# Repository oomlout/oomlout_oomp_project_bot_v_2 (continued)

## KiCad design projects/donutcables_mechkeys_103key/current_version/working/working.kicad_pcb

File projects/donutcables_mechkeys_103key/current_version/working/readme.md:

# mechkeys
 
## summary 
* id: donutcables_mechkeys_103key
* user: donutcables
* name: mechkeys
* board: 103key
* repo: https://github.com/DonutCables/mechkeys
* src_file_repo_kicad_pcb: 103key-project/103key.kicad_pcb
* src_file_repo_kicad_pcb_link: https://github.com/DonutCables/mechkeys/tree/master/103key-project/103key.kicad_pcb

* src_file_repo_sch: 103key-project/103key.sch
* src_file_repo_sch_link: https://github.com/DonutCables/mechkeys/tree/master/103key-project/103key.sch
* full details link: https://github.com/oomlout/oomlout_oomp_project_bot_v_2/tree/main/projects/donutcables_mechkeys_103key/current_version/working

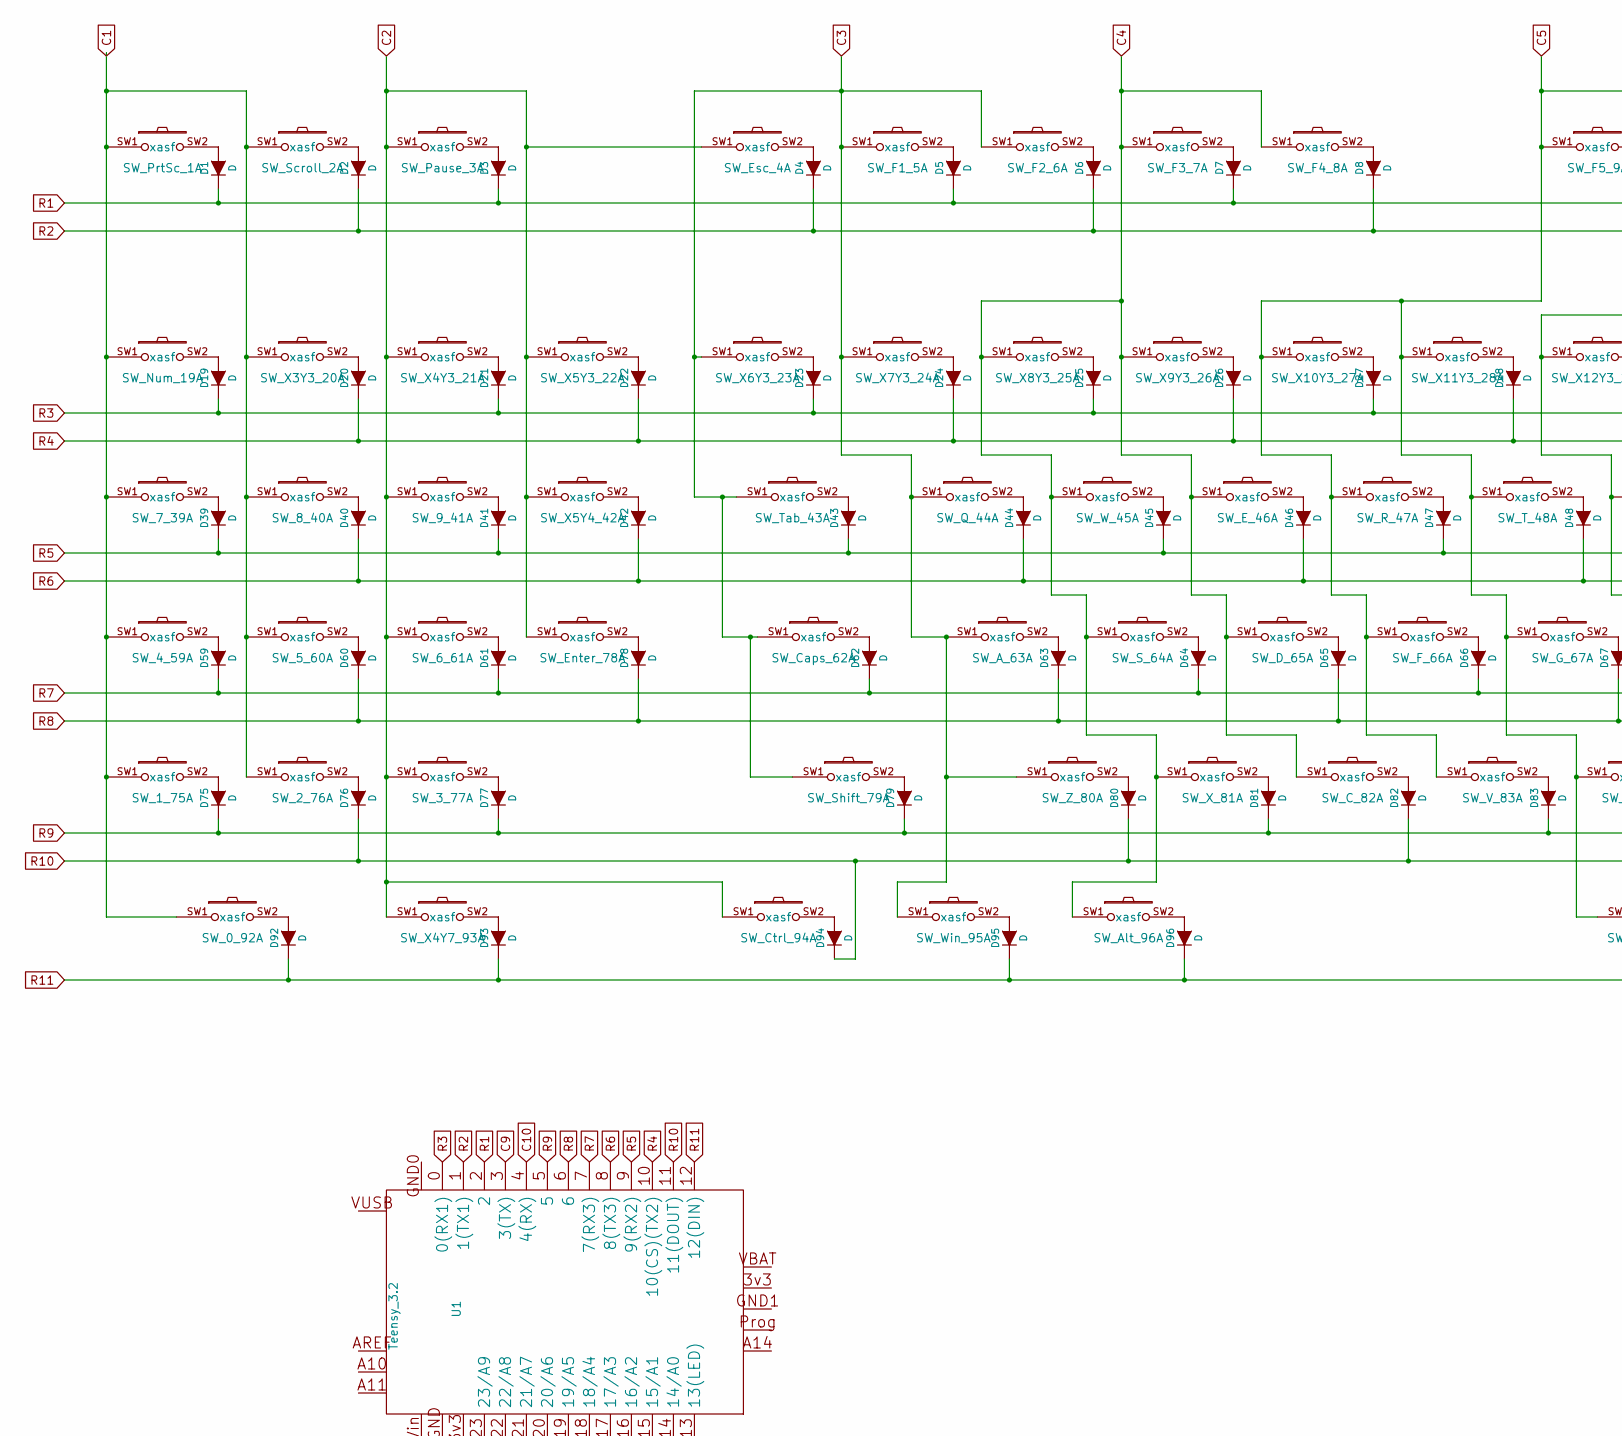
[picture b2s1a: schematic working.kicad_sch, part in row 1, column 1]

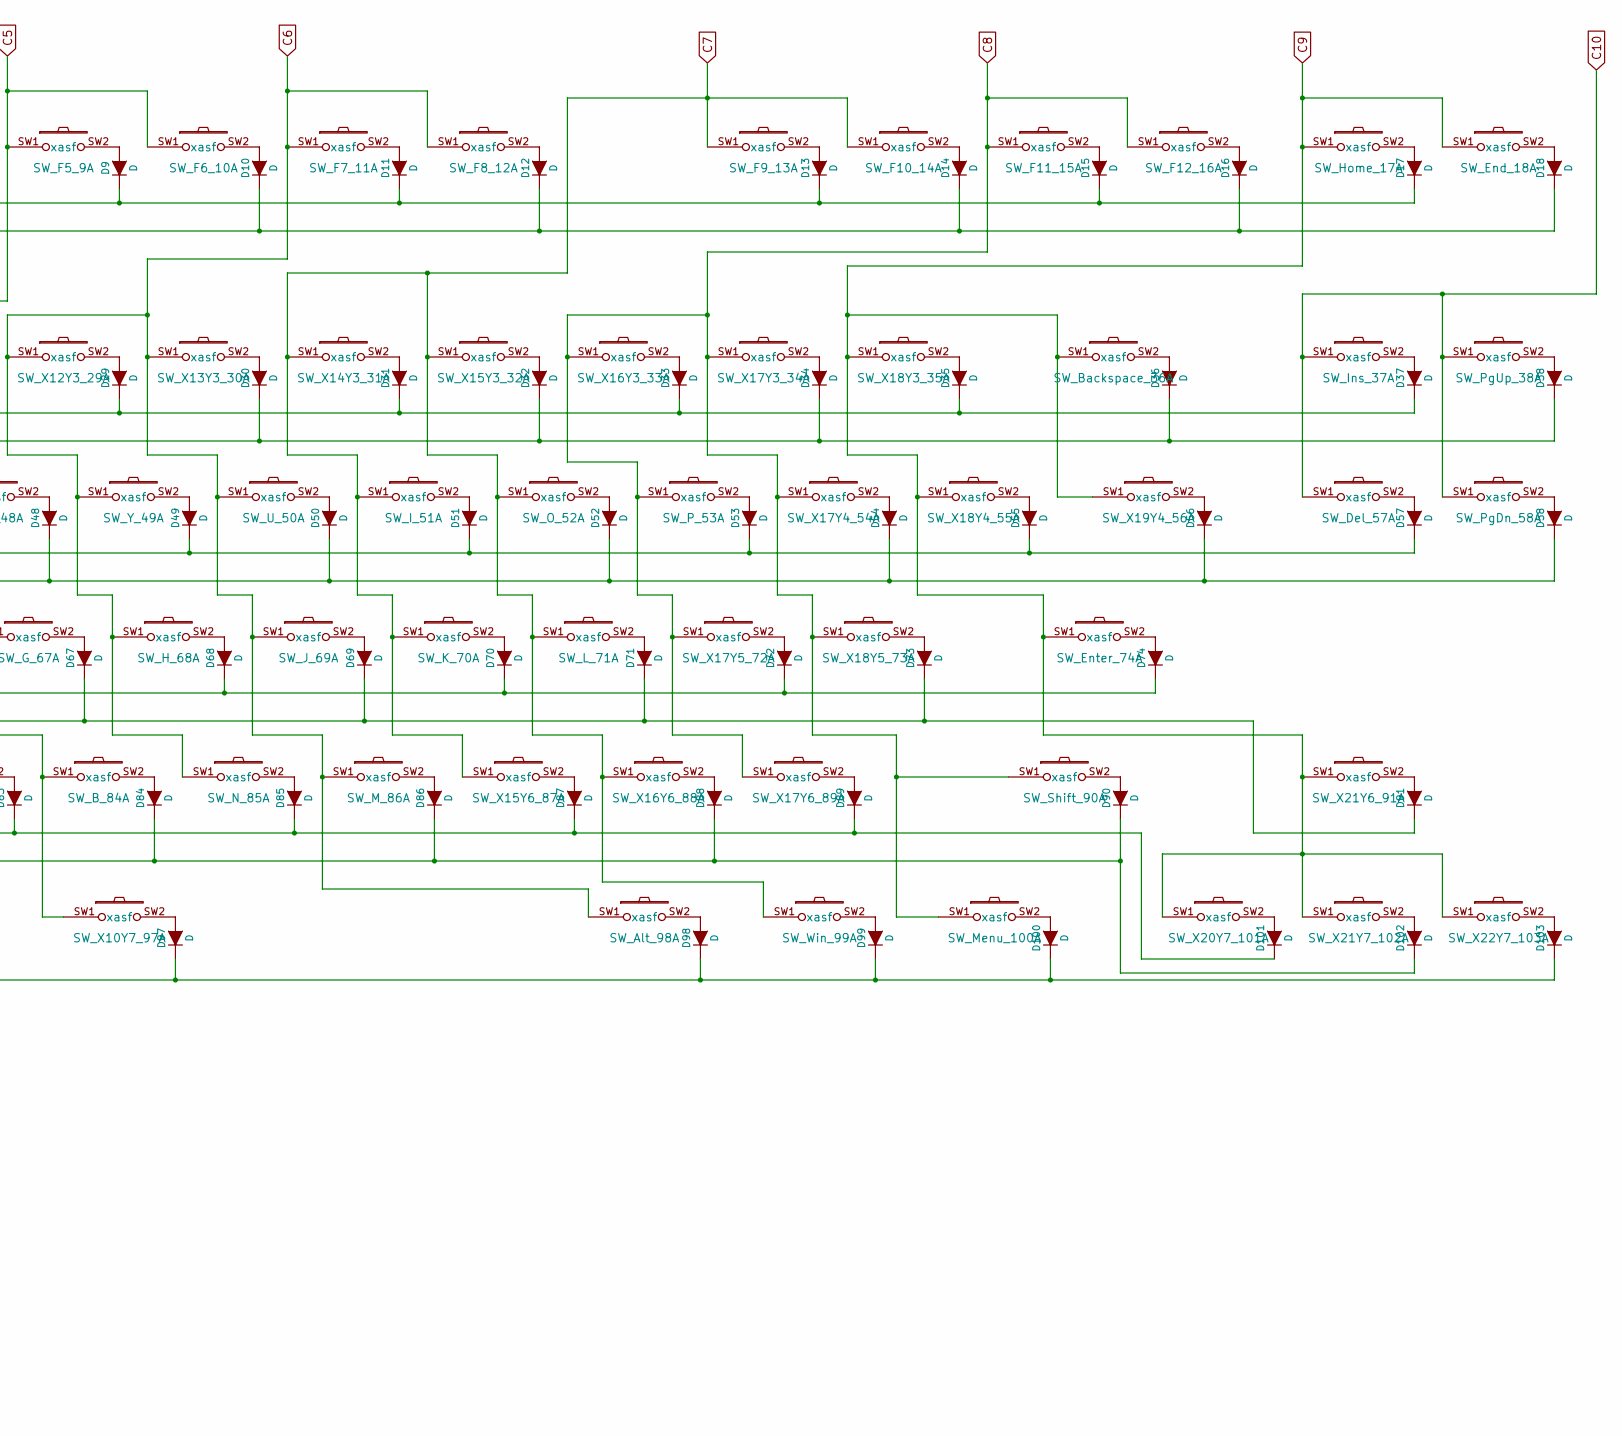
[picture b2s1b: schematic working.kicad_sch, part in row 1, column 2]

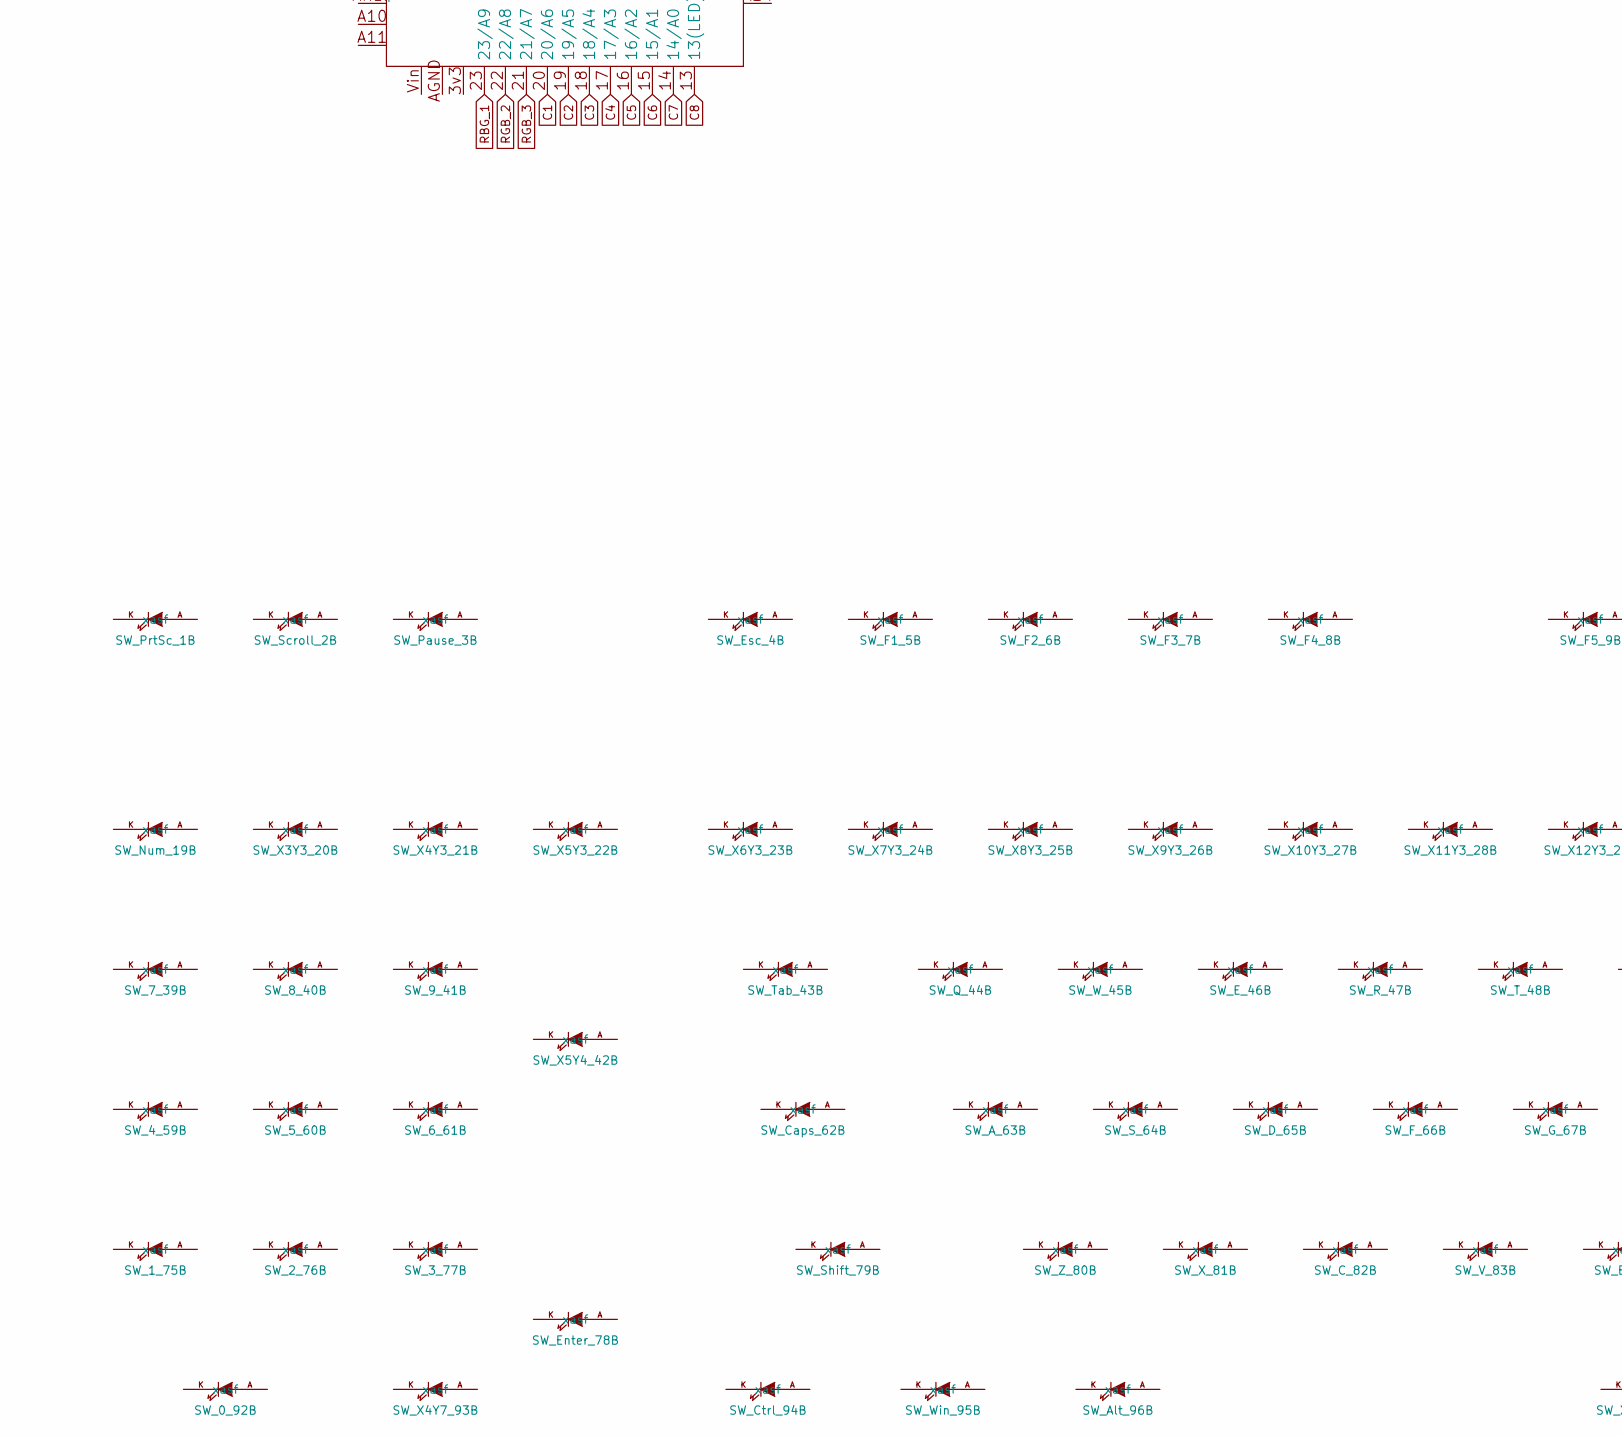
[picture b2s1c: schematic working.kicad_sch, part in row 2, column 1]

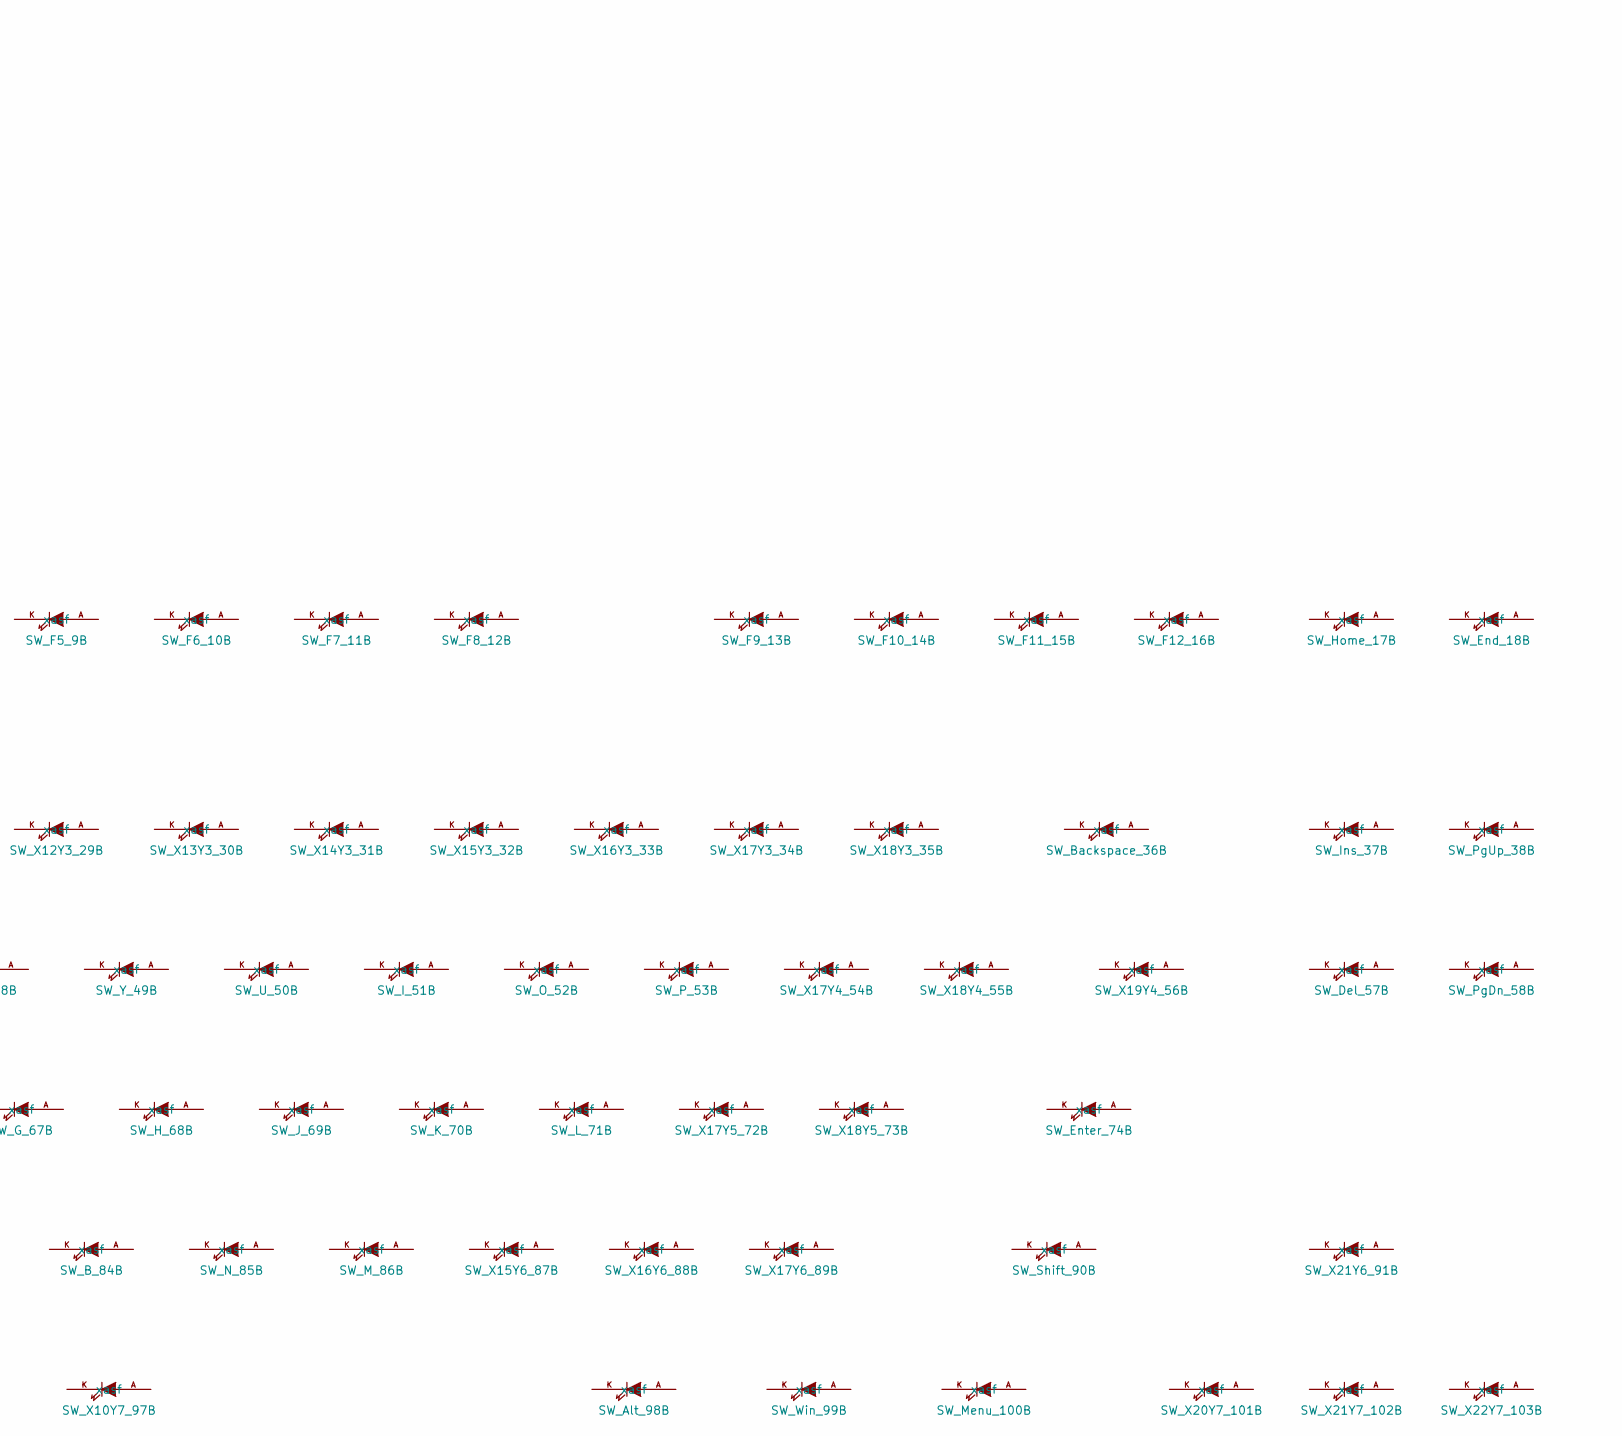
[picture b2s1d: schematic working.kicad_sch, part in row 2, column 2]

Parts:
D1, D2, D3, D4, D5, D6, D7, D8, D9, D10, D11, D12, D13, D14, D15, D16, D17, D18, D19, D20, D21, D22, D23, D24, D25, D26, D27, D28, D29, D30, D31, D32, D33, D34, D35, D36, D37, D38, D39, D40, D41, D42, D43, D44, D45, D46, D47, D48, D49, D50, D51, D52, D53, D54, D55, D56, D57, D58, D59, D60, D61, D62, D63, D64, D65, D66, D67, D68, D69, D70, D71, D72, D73, D74, D75, D76, D77, D78, D79, D80, D81, D82, D83, D84, D85, D86, D87, D88, D89, D90, D91, D92, D93, D94, D95, D96, D97, D98, D99, D100, D101, D102, D103: D
SW_0_92, SW_1_75, SW_2_76, SW_3_77, SW_4_59, SW_5_60, SW_6_61, SW_7_39, SW_8_40, SW_9_41: MX_LED
SW_A_63: MX_LED
SW_Alt_96, SW_Alt_98: MX_LED
SW_B_84: MX_LED
SW_Backspace_36: MX_LED
SW_C_82: MX_LED
SW_Caps_62: MX_LED
SW_Ctrl_94: MX_LED
SW_D_65: MX_LED
SW_Del_57: MX_LED
SW_E_46: MX_LED
SW_End_18: MX_LED
SW_Enter_74, SW_Enter_78: MX_LED
SW_Esc_4: MX_LED
SW_F1_5, SW_F2_6, SW_F3_7, SW_F4_8, SW_F5_9, SW_F6_10, SW_F7_11, SW_F8_12, SW_F9_13, SW_F10_14, SW_F11_15, SW_F12_16: MX_LED
SW_F_66: MX_LED
SW_G_67: MX_LED
SW_H_68: MX_LED
SW_Home_17: MX_LED
SW_I_51: MX_LED
SW_Ins_37: MX_LED
SW_J_69: MX_LED
SW_K_70: MX_LED
SW_L_71: MX_LED
SW_M_86: MX_LED
SW_Menu_100: MX_LED
SW_N_85: MX_LED
SW_Num_19: MX_LED
SW_O_52: MX_LED
SW_P_53: MX_LED
SW_Pause_3: MX_LED
SW_PgDn_58: MX_LED
SW_PgUp_38: MX_LED
SW_PrtSc_1: MX_LED
SW_Q_44: MX_LED
SW_R_47: MX_LED
SW_S_64: MX_LED
SW_Scroll_2: MX_LED
SW_Shift_79, SW_Shift_90: MX_LED
SW_T_48: MX_LED
SW_Tab_43: MX_LED
SW_U_50: MX_LED
SW_V_83: MX_LED
SW_W_45: MX_LED
SW_Win_95, SW_Win_99: MX_LED
SW_X3Y3_20, SW_X4Y3_21, SW_X4Y7_93, SW_X5Y3_22, SW_X5Y4_42, SW_X6Y3_23, SW_X7Y3_24, SW_X8Y3_25, SW_X9Y3_26, SW_X10Y3_27, SW_X10Y7_97, SW_X11Y3_28, SW_X12Y3_29, SW_X13Y3_30, SW_X14Y3_31, SW_X15Y3_32, SW_X15Y6_87, SW_X16Y3_33, SW_X16Y6_88, SW_X17Y3_34, SW_X17Y4_54, SW_X17Y5_72, SW_X17Y6_89, SW_X18Y3_35, SW_X18Y4_55, SW_X18Y5_73, SW_X19Y4_56, SW_X20Y7_101, SW_X21Y6_91, SW_X21Y7_102, SW_X22Y7_103: MX_LED
SW_X_81: MX_LED
SW_Y_49: MX_LED
SW_Z_80: MX_LED
U1: Teensy_3.2; Teensy3.2

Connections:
C1: SW_0_92.SW1, SW_1_75.SW1, SW_2_76.SW1, SW_4_59.SW1, SW_5_60.SW1, SW_7_39.SW1, SW_8_40.SW1, SW_Num_19.SW1, SW_PrtSc_1.SW1, SW_Scroll_2.SW1, SW_X3Y3_20.SW1, U1.20 (20/A6)
C2: SW_3_77.SW1, SW_6_61.SW1, SW_9_41.SW1, SW_Ctrl_94.SW1, SW_Enter_78.SW1, SW_Esc_4.SW1, SW_Pause_3.SW1, SW_X4Y3_21.SW1, SW_X4Y7_93.SW1, SW_X5Y3_22.SW1, SW_X5Y4_42.SW1, U1.19 (19/A5)
C3: SW_A_63.SW1, SW_Caps_62.SW1, SW_F1_5.SW1, SW_F2_6.SW1, SW_Q_44.SW1, SW_Shift_79.SW1, SW_Tab_43.SW1, SW_Win_95.SW1, SW_X6Y3_23.SW1, SW_X7Y3_24.SW1, SW_Z_80.SW1, U1.18 (18/A4)
C4: SW_Alt_96.SW1, SW_C_82.SW1, SW_D_65.SW1, SW_E_46.SW1, SW_F3_7.SW1, SW_F4_8.SW1, SW_S_64.SW1, SW_W_45.SW1, SW_X8Y3_25.SW1, SW_X9Y3_26.SW1, SW_X_81.SW1, U1.17 (17/A3)
C5: SW_B_84.SW1, SW_F5_9.SW1, SW_F6_10.SW1, SW_F_66.SW1, SW_G_67.SW1, SW_R_47.SW1, SW_T_48.SW1, SW_V_83.SW1, SW_X10Y3_27.SW1, SW_X10Y7_97.SW1, SW_X11Y3_28.SW1, U1.16 (16/A2)
C6: SW_Alt_98.SW1, SW_F7_11.SW1, SW_F8_12.SW1, SW_H_68.SW1, SW_J_69.SW1, SW_M_86.SW1, SW_N_85.SW1, SW_U_50.SW1, SW_X12Y3_29.SW1, SW_X13Y3_30.SW1, SW_Y_49.SW1, U1.15 (15/A1)
C7: SW_F9_13.SW1, SW_F10_14.SW1, SW_I_51.SW1, SW_K_70.SW1, SW_L_71.SW1, SW_O_52.SW1, SW_Win_99.SW1, SW_X14Y3_31.SW1, SW_X15Y3_32.SW1, SW_X15Y6_87.SW1, SW_X16Y6_88.SW1, U1.14 (14/A0)
C8: SW_F11_15.SW1, SW_F12_16.SW1, SW_Menu_100.SW1, SW_P_53.SW1, SW_Shift_90.SW1, SW_X16Y3_33.SW1, SW_X17Y3_34.SW1, SW_X17Y4_54.SW1, SW_X17Y5_72.SW1, SW_X17Y6_89.SW1, SW_X18Y5_73.SW1, U1.13 (13(LED))
C9: SW_Backspace_36.SW1, SW_End_18.SW1, SW_Enter_74.SW1, SW_Home_17.SW1, SW_X18Y3_35.SW1, SW_X18Y4_55.SW1, SW_X19Y4_56.SW1, SW_X20Y7_101.SW1, SW_X21Y6_91.SW1, SW_X21Y7_102.SW1, SW_X22Y7_103.SW1, U1.3 (3(TX))
C10: SW_Del_57.SW1, SW_Ins_37.SW1, SW_PgDn_58.SW1, SW_PgUp_38.SW1, U1.4 (4(RX))
unnamed: D1.2 (A), SW_PrtSc_1.SW2
unnamed: D2.2 (A), SW_Scroll_2.SW2
unnamed: D3.2 (A), SW_Pause_3.SW2
unnamed: D4.2 (A), SW_Esc_4.SW2
unnamed: D5.2 (A), SW_F1_5.SW2
unnamed: D6.2 (A), SW_F2_6.SW2
unnamed: D7.2 (A), SW_F3_7.SW2
unnamed: D8.2 (A), SW_F4_8.SW2
unnamed: D9.2 (A), SW_F5_9.SW2
unnamed: D10.2 (A), SW_F6_10.SW2
unnamed: D11.2 (A), SW_F7_11.SW2
unnamed: D12.2 (A), SW_F8_12.SW2
unnamed: D13.2 (A), SW_F9_13.SW2
unnamed: D14.2 (A), SW_F10_14.SW2
unnamed: D15.2 (A), SW_F11_15.SW2
unnamed: D16.2 (A), SW_F12_16.SW2
unnamed: D17.2 (A), SW_Home_17.SW2
unnamed: D18.2 (A), SW_End_18.SW2
unnamed: D19.2 (A), SW_Num_19.SW2
unnamed: D20.2 (A), SW_X3Y3_20.SW2
unnamed: D21.2 (A), SW_X4Y3_21.SW2
unnamed: D22.2 (A), SW_X5Y3_22.SW2
unnamed: D23.2 (A), SW_X6Y3_23.SW2
unnamed: D24.2 (A), SW_X7Y3_24.SW2
unnamed: D25.2 (A), SW_X8Y3_25.SW2
unnamed: D26.2 (A), SW_X9Y3_26.SW2
unnamed: D27.2 (A), SW_X10Y3_27.SW2
unnamed: D28.2 (A), SW_X11Y3_28.SW2
unnamed: D29.2 (A), SW_X12Y3_29.SW2
unnamed: D30.2 (A), SW_X13Y3_30.SW2
unnamed: D31.2 (A), SW_X14Y3_31.SW2
unnamed: D32.2 (A), SW_X15Y3_32.SW2
unnamed: D33.2 (A), SW_X16Y3_33.SW2
unnamed: D34.2 (A), SW_X17Y3_34.SW2
unnamed: D35.2 (A), SW_X18Y3_35.SW2
unnamed: D36.2 (A), SW_Backspace_36.SW2
unnamed: D37.2 (A), SW_Ins_37.SW2
unnamed: D38.2 (A), SW_PgUp_38.SW2
unnamed: D39.2 (A), SW_7_39.SW2
unnamed: D40.2 (A), SW_8_40.SW2
unnamed: D41.2 (A), SW_9_41.SW2
unnamed: D42.2 (A), SW_X5Y4_42.SW2
unnamed: D43.2 (A), SW_Tab_43.SW2
unnamed: D44.2 (A), SW_Q_44.SW2
unnamed: D45.2 (A), SW_W_45.SW2
unnamed: D46.2 (A), SW_E_46.SW2
unnamed: D47.2 (A), SW_R_47.SW2
unnamed: D48.2 (A), SW_T_48.SW2
unnamed: D49.2 (A), SW_Y_49.SW2
unnamed: D50.2 (A), SW_U_50.SW2
unnamed: D51.2 (A), SW_I_51.SW2
unnamed: D52.2 (A), SW_O_52.SW2
unnamed: D53.2 (A), SW_P_53.SW2
unnamed: D54.2 (A), SW_X17Y4_54.SW2
unnamed: D55.2 (A), SW_X18Y4_55.SW2
unnamed: D56.2 (A), SW_X19Y4_56.SW2
unnamed: D57.2 (A), SW_Del_57.SW2
unnamed: D58.2 (A), SW_PgDn_58.SW2
unnamed: D59.2 (A), SW_4_59.SW2
unnamed: D60.2 (A), SW_5_60.SW2
unnamed: D61.2 (A), SW_6_61.SW2
unnamed: D62.2 (A), SW_Caps_62.SW2
unnamed: D63.2 (A), SW_A_63.SW2
unnamed: D64.2 (A), SW_S_64.SW2
unnamed: D65.2 (A), SW_D_65.SW2
unnamed: D66.2 (A), SW_F_66.SW2
unnamed: D67.2 (A), SW_G_67.SW2
unnamed: D68.2 (A), SW_H_68.SW2
unnamed: D69.2 (A), SW_J_69.SW2
unnamed: D70.2 (A), SW_K_70.SW2
unnamed: D71.2 (A), SW_L_71.SW2
unnamed: D72.2 (A), SW_X17Y5_72.SW2
unnamed: D73.2 (A), SW_X18Y5_73.SW2
unnamed: D74.2 (A), SW_Enter_74.SW2
unnamed: D75.2 (A), SW_1_75.SW2
unnamed: D76.2 (A), SW_2_76.SW2
unnamed: D77.2 (A), SW_3_77.SW2
unnamed: D78.2 (A), SW_Enter_78.SW2
unnamed: D79.2 (A), SW_Shift_79.SW2
unnamed: D80.2 (A), SW_Z_80.SW2
unnamed: D81.2 (A), SW_X_81.SW2
unnamed: D82.2 (A), SW_C_82.SW2
unnamed: D83.2 (A), SW_V_83.SW2
unnamed: D84.2 (A), SW_B_84.SW2
unnamed: D85.2 (A), SW_N_85.SW2
unnamed: D86.2 (A), SW_M_86.SW2
unnamed: D87.2 (A), SW_X15Y6_87.SW2
unnamed: D88.2 (A), SW_X16Y6_88.SW2
unnamed: D89.2 (A), SW_X17Y6_89.SW2
unnamed: D90.2 (A), SW_Shift_90.SW2
unnamed: D91.2 (A), SW_X21Y6_91.SW2
unnamed: D92.2 (A), SW_0_92.SW2
unnamed: D93.2 (A), SW_X4Y7_93.SW2
unnamed: D94.2 (A), SW_Ctrl_94.SW2
unnamed: D95.2 (A), SW_Win_95.SW2
unnamed: D96.2 (A), SW_Alt_96.SW2
unnamed: D97.2 (A), SW_X10Y7_97.SW2
unnamed: D98.2 (A), SW_Alt_98.SW2
unnamed: D99.2 (A), SW_Win_99.SW2
unnamed: D100.2 (A), SW_Menu_100.SW2
unnamed: D101.2 (A), SW_X20Y7_101.SW2
unnamed: D102.2 (A), SW_X21Y7_102.SW2
unnamed: D103.2 (A), SW_X22Y7_103.SW2
R1: D1.1 (K), D3.1 (K), D5.1 (K), D7.1 (K), D9.1 (K), D11.1 (K), D13.1 (K), D15.1 (K), D17.1 (K), U1.2
R2: D2.1 (K), D4.1 (K), D6.1 (K), D8.1 (K), D10.1 (K), D12.1 (K), D14.1 (K), D16.1 (K), D18.1 (K), U1.1 (1(TX1))
R3: D19.1 (K), D21.1 (K), D23.1 (K), D25.1 (K), D27.1 (K), D29.1 (K), D31.1 (K), D33.1 (K), D35.1 (K), D37.1 (K), U1.0 (0(RX1))
R4: D20.1 (K), D22.1 (K), D24.1 (K), D26.1 (K), D28.1 (K), D30.1 (K), D32.1 (K), D34.1 (K), D36.1 (K), D38.1 (K), U1.10 (10(CS)(TX2))
R5: D39.1 (K), D41.1 (K), D43.1 (K), D45.1 (K), D47.1 (K), D49.1 (K), D51.1 (K), D53.1 (K), D55.1 (K), D57.1 (K), U1.9 (9(RX2))
R6: D40.1 (K), D42.1 (K), D44.1 (K), D46.1 (K), D48.1 (K), D50.1 (K), D52.1 (K), D54.1 (K), D56.1 (K), D58.1 (K), U1.8 (8(TX3))
R7: D59.1 (K), D61.1 (K), D62.1 (K), D64.1 (K), D66.1 (K), D68.1 (K), D70.1 (K), D72.1 (K), D74.1 (K), U1.7 (7(RX3))
R8: D60.1 (K), D63.1 (K), D65.1 (K), D67.1 (K), D69.1 (K), D71.1 (K), D73.1 (K), D78.1 (K), D91.1 (K), U1.6
R9: D75.1 (K), D77.1 (K), D79.1 (K), D81.1 (K), D83.1 (K), D85.1 (K), D87.1 (K), D89.1 (K), D101.1 (K), U1.5
R10: D76.1 (K), D80.1 (K), D82.1 (K), D84.1 (K), D86.1 (K), D88.1 (K), D90.1 (K), D94.1 (K), D102.1 (K), U1.11 (11(DOUT))
R11: D92.1 (K), D93.1 (K), D95.1 (K), D96.1 (K), D97.1 (K), D98.1 (K), D99.1 (K), D100.1 (K), D103.1 (K), U1.12 (12(DIN))

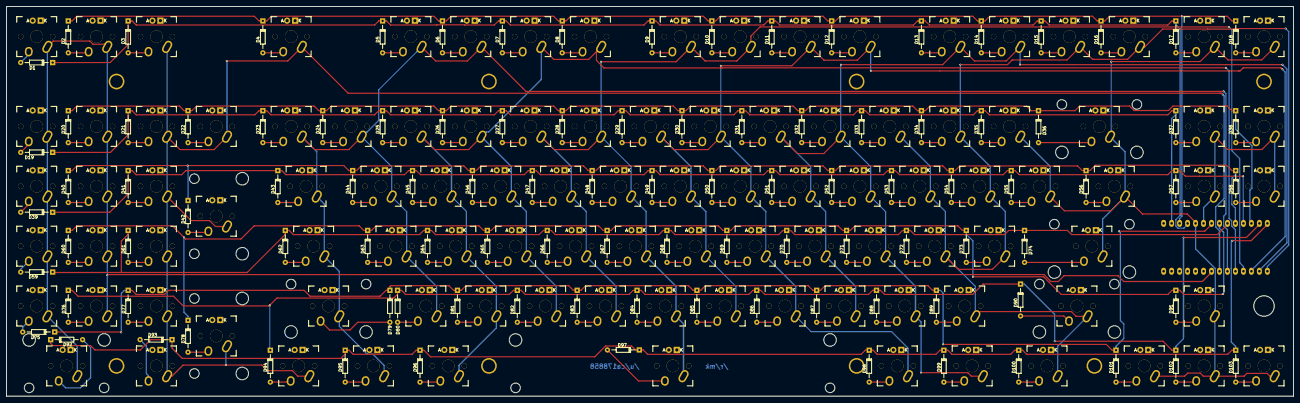
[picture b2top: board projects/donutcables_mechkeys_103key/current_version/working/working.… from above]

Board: 2 copper layers, 409.5 x 124.0 mm, 215 parts (1 on the bottom side), 124 nets.

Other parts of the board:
CHERRY: MX; CHERRY_PCB_200H_STABILIZER
CHERRY#2, CHERRY#6: MX; CHERRY_PCB_225H_STABILIZER
CHERRY#3: MX; CHERRY_PCB_625H_STABILIZER
CHERRY#4: MX; CHERRY_PCB_200H_STABILIZER
CHERRY#5: MX; CHERRY_PCB_275H_STABILIZER
STA: Stabilizer; CHERRY_PCB_200_STABILIZER
STA#2: Stabilizer; CHERRY_PCB_200_STABILIZER

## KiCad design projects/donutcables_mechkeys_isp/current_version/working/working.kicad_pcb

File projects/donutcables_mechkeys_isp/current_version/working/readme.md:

# mechkeys
 
## summary 
* id: donutcables_mechkeys_isp
* user: donutcables
* name: mechkeys
* board: isp
* repo: https://github.com/DonutCables/mechkeys
* src_file_repo_kicad_pcb: isp/isp.kicad_pcb
* src_file_repo_kicad_pcb_link: https://github.com/DonutCables/mechkeys/tree/master/isp/isp.kicad_pcb

* src_file_repo_sch: isp/isp.sch
* src_file_repo_sch_link: https://github.com/DonutCables/mechkeys/tree/master/isp/isp.sch
* full details link: https://github.com/oomlout/oomlout_oomp_project_bot_v_2/tree/main/projects/donutcables_mechkeys_isp/current_version/working

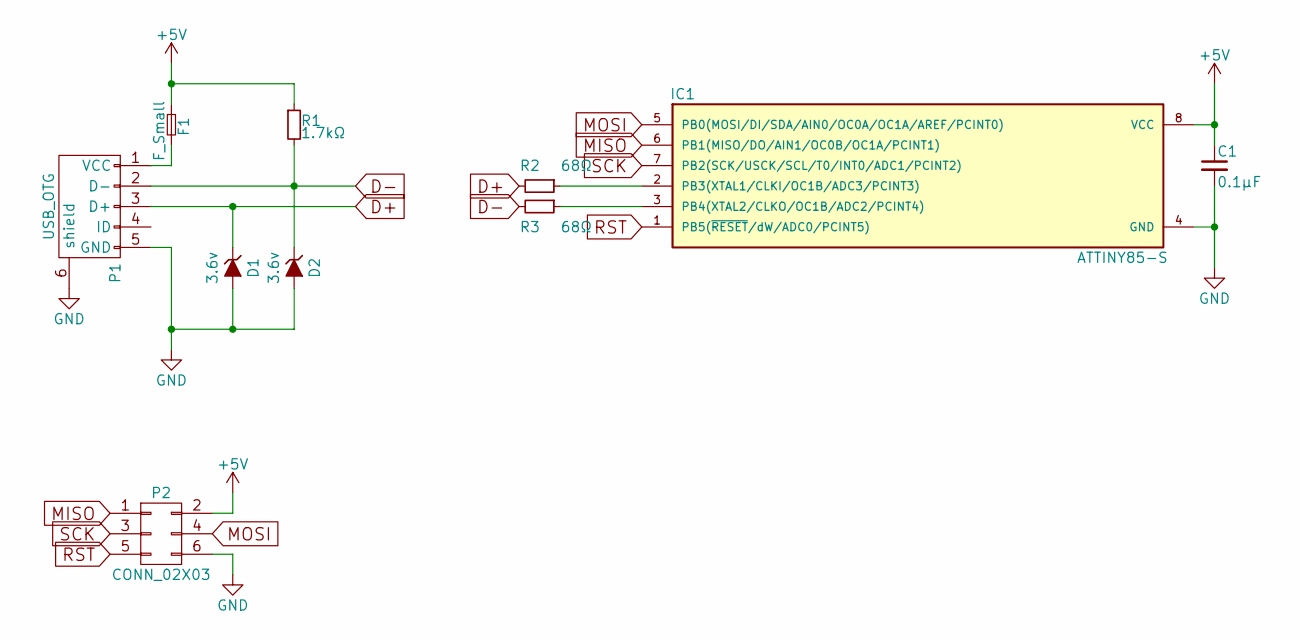
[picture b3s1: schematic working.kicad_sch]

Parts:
C1: 0.1µF; C_0805_HandSoldering; Mouser 80-C0805C104K5R
D1, D2: 3.6v; SOD-323_HandSoldering; Mouser 621-BZT52C3V6-F
F1: F_Small; Fuse_SMD1206_HandSoldering; Mouser 576-1206L050/15YR
IC1: ATTINY85-S; SOIJ-8_5.3x5.3mm_Pitch1.27mm; Mouser 556-ATTINY45-20SU
P1: USB_OTG; USB_Mini-B; Mouser 649-10033526-N3212LF
P2: CONN_02X03; Pin_Header_Straight_2x03
R1: 1.7kΩ; R_0805_HandSoldering
R2, R3: 68Ω; R_0805_HandSoldering; Mouser 667-ERJ-6GEYJ680V

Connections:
+5V: C1.1, F1.1, IC1.8 (VCC), P2.2, R1.1
D+: D1.1 (K), P1.3 (D+), R2.2
D-: D2.1 (K), P1.2 (D-), R1.2, R3.2
GND: C1.2, D1.2 (A), D2.2 (A), IC1.4 (GND), P1.5 (GND), P1.6 (shield), P2.6
MISO: IC1.6 (PB1(MISO/DO/AIN1/OC0B/OC1A/PCINT1)), P2.1
MOSI: IC1.5 (PB0(MOSI/DI/SDA/AIN0/OC0A/OC1A/AREF/PCI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), P2.4
unnamed: F1.2, P1.1 (VCC)
unnamed: IC1.2 (PB3(XTAL1/CLKI/OC1B/ADC3/PCINT3)), R2.1
unnamed: IC1.3 (PB4(XTAL2/CLKO/OC1B/ADC2/PCINT4)), R3.1
RST: IC1.1 (PB5(~RESET/dW/ADC0/PCINT5)), P2.5
SCK: IC1.7 (PB2(SCK/USCK/SCL/T0/INT0/ADC1/PCINT2)), P2.3

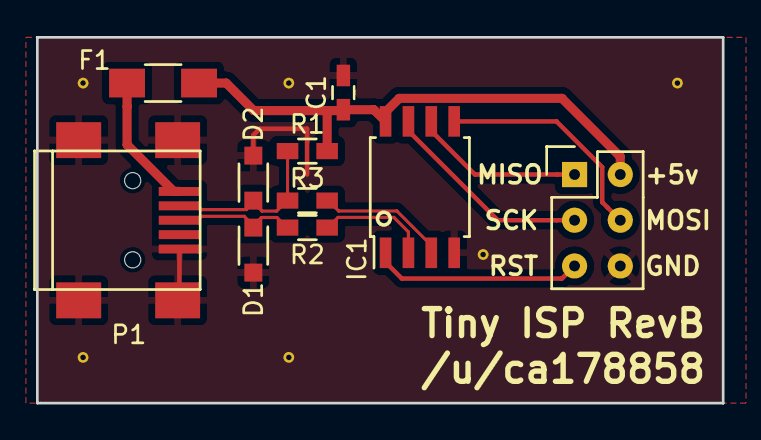
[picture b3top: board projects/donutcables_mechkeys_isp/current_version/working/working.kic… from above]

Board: 2 copper layers, 38.1 x 20.3 mm, 10 parts (0 on the bottom side), 11 nets.

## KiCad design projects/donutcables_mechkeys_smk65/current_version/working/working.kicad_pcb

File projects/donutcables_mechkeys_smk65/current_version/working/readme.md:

# mechkeys
 
## summary 
* id: donutcables_mechkeys_smk65
* user: donutcables
* name: mechkeys
* board: smk65
* repo: https://github.com/DonutCables/mechkeys
* src_file_repo_kicad_pcb: smk65/smk65.kicad_pcb
* src_file_repo_kicad_pcb_link: https://github.com/DonutCables/mechkeys/tree/master/smk65/smk65.kicad_pcb

* src_file_repo_sch: isp/isp.sch
* src_file_repo_sch_link: https://github.com/DonutCables/mechkeys/tree/master/isp/isp.sch
* full details link: https://github.com/oomlout/oomlout_oomp_project_bot_v_2/tree/main/projects/donutcables_mechkeys_smk65/current_version/working

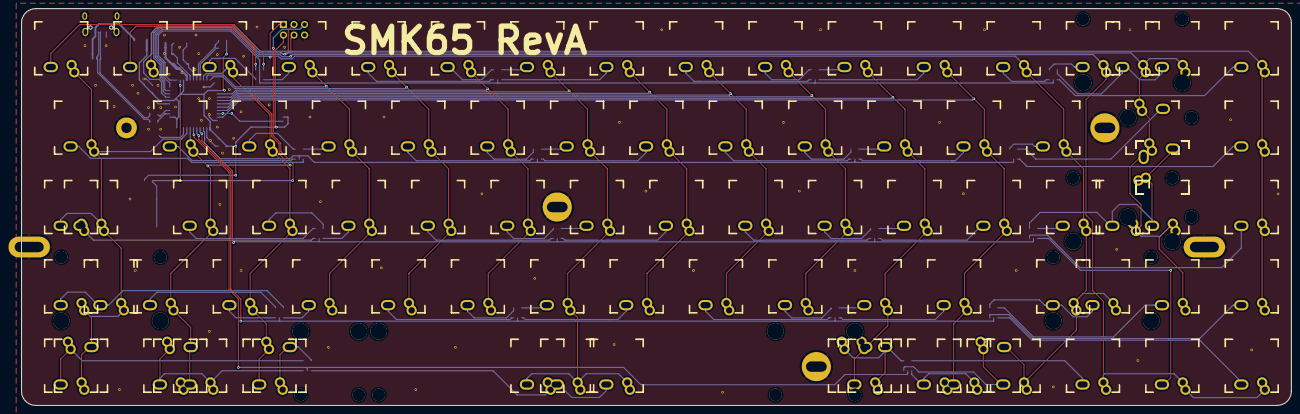
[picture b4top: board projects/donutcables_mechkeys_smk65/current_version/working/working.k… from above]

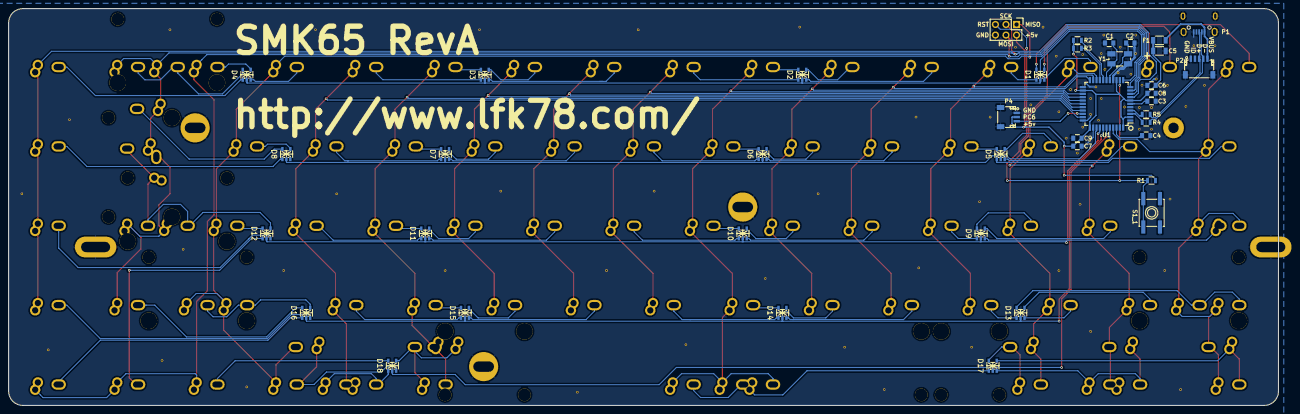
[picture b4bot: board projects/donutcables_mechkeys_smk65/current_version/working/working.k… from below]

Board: 2 copper layers, 304.8 x 95.2 mm, 149 parts (40 on the bottom side), 107 nets.

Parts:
C1, C2: 18pF; C_0805
C3, C6, C7, C8, C9: 0.1µF; C_0805
C4: 1µF; C_0805
C5: 4.7µF; C_1206
D1, D2, D3, D4, D5, D6, D7, D8, D9, D10, D11, D12, D13, D14, D15, D16, D17, D18: 1SS309; SC-74A
F1: FP_Small; C_1206
MH1, MH2, MH3: MOUNT_HOLE; PKRH
MH4: MOUNT_HOLE; PKRHC
MH5, MH6: MOUNT_HOLE; PKRHSL
P1: USB_OTG; USB2_MICROB_WURTH
P2: CONN_01X05; JST_SH_SM05B-SRSS-TB_05x1.00mm_Angled
P3: CONN_02X03; Pin_Header_Straight_2x03
P4: CONN_01X03; JST_SH_SM03B-SRSS-TB_03x1.00mm_Angled
R1: 10k; R_0805
R2, R3: 4.7k; R_0805
R4, R5: 22; R_0805
S1, S2, S3, S4, S5, S6, S7, S8, S9, S10, S11, S12, S13, S14, S15, S16, S17, S18, S19, S20, S21, S22, S23, S24, S25, S26, S27, S28, S29, S30, S31, S32, S33, S34, S35, S36, S37, S38, S39, S40, S41, S42, S43, S44, S45, S46, S47, S48, S49, S50, S51, S52, S53, S54, S55, S56, S57, S58, S59, S60, S61, S62, S63, S64, S65, S66, S67, S68, S69, S70, S71, S115, S132, S145, S147, S159, S162, S163, S164, S165, S166, S167, S168, S245, S263, S265, S266, S345: MX_LED; SMK-Alps
S1_1: SW_PUSH; SW_SPST_EVQP0
STAB1, STAB2, STAB3, STAB4, STAB5, STAB6, STAB7, STAB8, STAB9, STAB10, STAB11, STAB12, STAB13, STAB14, STAB15: STAB
U1: ATmega32U4-AU; TQFP-44_10x10mm_Pitch0.8mm
Y1: CRYSTAL_SMD; Crystal_SMD_5032_4Pads

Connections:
+5v: C5.1, C6.1, C7.1, C8.1, C9.1, F1.2, P3.2, P4.2, R1.1, R2.1, R3.1, U1.2, U1.7, U1.14, U1.24, U1.34, U1.44
C1: S1.SW1, S17.SW1, S32.SW1, S47.SW1, S62.SW1, S132.SW2, S147.SW1, S162.SW2, U1.41
C2: S2.SW1, S18.SW1, S33.SW1, S48.SW1, S63.SW1, S163.SW2, S263.SW2, U1.40
C3: S3.SW1, S19.SW1, S34.SW1, S49.SW1, S64.SW2, S164.SW1, U1.20
C4: S4.SW1, S20.SW1, S35.SW1, S50.SW1, U1.21
C5: S5.SW1, S21.SW1, S36.SW1, S51.SW1, U1.22
C6: S6.SW1, S22.SW1, S37.SW1, S52.SW1, U1.25
C7: S7.SW1, S23.SW1, S38.SW1, S53.SW1, S65.SW1, S165.SW2, S265.SW1, U1.26
C8: S8.SW1, S24.SW1, S39.SW1, S54.SW1, U1.27
C9: S9.SW1, S25.SW1, S40.SW1, S55.SW1, U1.28
C10: S10.SW1, S26.SW1, S41.SW1, S56.SW1, U1.29
C11: S11.SW1, S27.SW1, S42.SW1, S57.SW1, S66.SW2, S166.SW2, S266.SW1, U1.30
C12: S12.SW1, S28.SW1, S43.SW1, S58.SW1, S67.SW1, S167.SW2, U1.32
C13: P3.1, S13.SW1, S29.SW1, S44.SW1, S59.SW1, S68.SW1, S159.SW1, S168.SW2, U1.11
C14: P3.4, S14.SW1, S69.SW1, S70.SW1, S71.SW1, U1.10
C15: P3.3, S15.SW1, S30.SW1, S45.SW1, S60.SW1, S115.SW1, S145.SW1, S245.SW2, S345.SW1, U1.9
C16: S16.SW1, S31.SW1, S46.SW1, S61.SW1, U1.8
D+: R5.1, U1.4
D-: R4.1, U1.3
GND: C1.1, C2.1, C3.2, C4.2, C5.2, C6.2, C7.2, C8.2, C9.2, MH1.1, MH2.1, MH3.1, MH4.1, MH5.1, MH6.1, P1.5, P2.1, P3.6, P4.1, S1_1.2, U1.5, U1.15, U1.23, U1.33, U1.35, U1.43, Y1.3
LED_SCL: R2.2, U1.18
LED_SDA: R3.2, U1.19
Matrix-S1-D1-5: D1.5, S1.SW2
Matrix-S2-D1-4: D1.4, S2.SW2
Matrix-S3-D1-3: D1.3, S3.SW2
Matrix-S4-D1-1: D1.1, S4.SW2
Matrix-S5-D2-3: D2.3, S5.SW2
Matrix-S6-D2-4: D2.4, S6.SW2
Matrix-S7-D2-5: D2.5, S7.SW2
Matrix-S8-D2-1: D2.1, S8.SW2
Matrix-S9-D3-3: D3.3, S9.SW2
Matrix-S10-D3-4: D3.4, S10.SW2
Matrix-S11-D3-5: D3.5, S11.SW2
Matrix-S12-D3-1: D3.1, S12.SW2
Matrix-S13-D4-3: D4.3, S13.SW2
Matrix-S14-D4-4: D4.4, S14.SW2
Matrix-S15-D4-5: D4.5, S15.SW2, S115.SW2
Matrix-S16-D4-1: D4.1, S16.SW2
Matrix-S17-D5-1: D5.1, S17.SW2
Matrix-S18-D5-3: D5.3, S18.SW2
Matrix-S19-D5-4: D5.4, S19.SW2
Matrix-S20-D5-5: D5.5, S20.SW2
Matrix-S21-D6-3: D6.3, S21.SW2
Matrix-S22-D6-4: D6.4, S22.SW2
Matrix-S23-D6-5: D6.5, S23.SW2
Matrix-S24-D6-1: D6.1, S24.SW2
Matrix-S25-D7-3: D7.3, S25.SW2
Matrix-S26-D7-4: D7.4, S26.SW2
Matrix-S27-D7-5: D7.5, S27.SW2
Matrix-S28-D7-1: D7.1, S28.SW2
Matrix-S29-D8-4: D8.4, S29.SW2
Matrix-S30-D8-5: D8.5, S30.SW2
Matrix-S31-D8-1: D8.1, S31.SW2
Matrix-S32-D9-3: D9.3, S32.SW2, S132.SW1
Matrix-S33-D9-4: D9.4, S33.SW2
Matrix-S34-D9-5: D9.5, S34.SW2
Matrix-S35-D9-1: D9.1, S35.SW2
Matrix-S36-D10-3: D10.3, S36.SW2
Matrix-S37-D10-4: D10.4, S37.SW2
Matrix-S38-D10-5: D10.5, S38.SW2
Matrix-S39-D10-1: D10.1, S39.SW2
Matrix-S40-D11-3: D11.3, S40.SW2
Matrix-S41-D11-4: D11.4, S41.SW2
Matrix-S42-D11-5: D11.5, S42.SW2
Matrix-S43-D11-1: D11.1, S43.SW2
Matrix-S44-D12-5: D12.5, S44.SW2
Matrix-S45-D12-4: D12.4, S45.SW2, S145.SW2, S245.SW1, S345.SW2
Matrix-S46-D12-3: D12.3, S46.SW2
Matrix-S47-D13-5: D13.5, S47.SW2, S147.SW2
Matrix-S48-D13-4: D13.4, S48.SW2
Matrix-S49-D13-3: D13.3, S49.SW2
Matrix-S50-D13-1: D13.1, S50.SW2
Matrix-S51-D14-3: D14.3, S51.SW2
Matrix-S52-D14-4: D14.4, S52.SW2
Matrix-S53-D14-5: D14.5, S53.SW2
Matrix-S54-D14-1: D14.1, S54.SW2
Matrix-S55-D15-3: D15.3, S55.SW2
Matrix-S56-D15-4: D15.4, S56.SW2
Matrix-S57-D15-5: D15.5, S57.SW2
Matrix-S58-D15-1: D15.1, S58.SW2
Matrix-S59-D16-4: D16.4, S59.SW2, S159.SW2
Matrix-S60-D16-5: D16.5, S60.SW2
Matrix-S61-D16-3: D16.3, S61.SW2
Matrix-S62-D17-4: D17.4, S62.SW2, S162.SW1
Matrix-S63-D17-3: D17.3, S63.SW2, S163.SW1, S263.SW1
Matrix-S64-D17-5: D17.5, S64.SW1, S164.SW2
Matrix-S65-D17-1: D17.1, S65.SW2, S165.SW1, S265.SW2
Matrix-S66-D18-4: D18.4, S66.SW1, S166.SW1, S266.SW2
Matrix-S67-D18-1: D18.1, S67.SW2, S167.SW1
Matrix-S68-D18-3: D18.3, S68.SW2, S168.SW1
Matrix-S69-D18-5: D18.5, S69.SW2
Matrix-S70-D12-1: D12.1, S70.SW2
Matrix-S71-D16-1: D16.1, S71.SW2
unnamed: C1.2, U1.17, Y1.1
unnamed: C2.2, U1.16, Y1.2
unnamed: C3.1, U1.6
unnamed: C4.1, U1.42
unnamed: P4.3, U1.31
R1: D1.2, D2.2, D3.2, D4.2, U1.12
R2: D5.2, D6.2, D7.2, D8.2, U1.36
R3: D9.2, D10.2, D11.2, D12.2, U1.37
R4: D13.2, D14.2, D15.2, D16.2, U1.38
R5: D17.2, D18.2, U1.39
RESET: P3.5, R1.2, S1_1.1, U1.13
USB+: P1.3, P2.3, R5.2
USB-: P1.2, P2.4, R4.2
VBUS: F1.1, P1.1, P2.5
